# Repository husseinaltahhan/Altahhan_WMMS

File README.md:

# Altahhan_WMMS
WMMS = Welding Machines Monitoring System

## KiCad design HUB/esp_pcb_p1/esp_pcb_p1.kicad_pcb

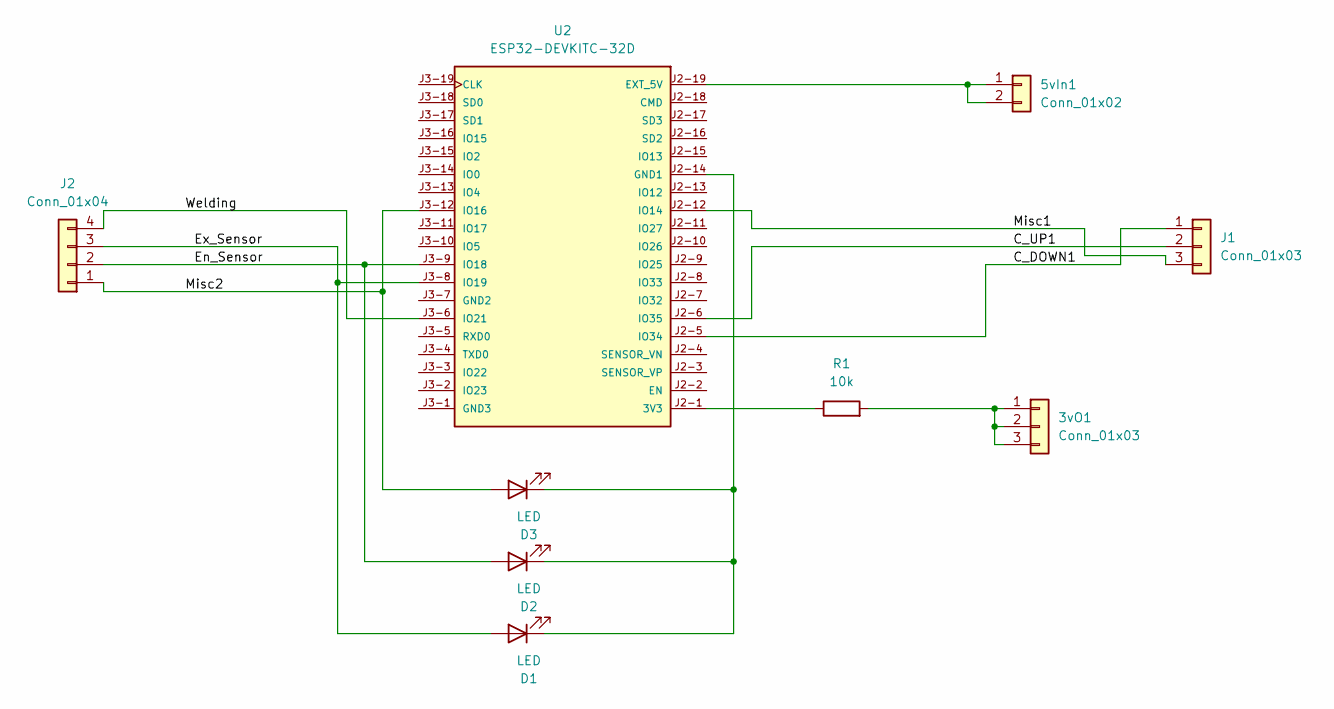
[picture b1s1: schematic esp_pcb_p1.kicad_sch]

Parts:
3vO1: Conn_01x03; TerminalBlock_Phoenix_MKDS-1,5-3-5.08_1x03_P5.08mm_Horizont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
5vIn1: Conn_01x02; TerminalBlock_Phoenix_MKDS-1,5-2-5.08_1x02_P5.08mm_Horizont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
D1, D2, D3: LED; LED_D5.0mm
J1: Conn_01x03; TerminalBlock_Phoenix_MKDS-1,5-3-5.08_1x03_P5.08mm_Horizont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
J2: Conn_01x04; TerminalBlock_Phoenix_MKDS-1,5-4-5.08_1x04_P5.08mm_Horizont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
R1: 10k; R_Axial_DIN0207_L6.3mm_D2.5mm_P7.62mm_Horizontal
U2: ESP32-DEVKITC-32D; MODULE_ESP32-DEVKITC-32D; PARTREV V4

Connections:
/C_DOWN1: J1.1, U2.J2-5 (IO34)
/C_UP1: J1.2, U2.J2-6 (IO35)
/En_Sensor: D2.2 (A), J2.2, U2.J3-9 (IO18)
/Ex_Sensor: D1.2 (A), J2.3, U2.J3-8 (IO19)
/Misc1: J1.3, U2.J2-12 (IO14)
/Misc2: D3.2 (A), J2.1, U2.J3-12 (IO16)
/Welding: J2.4, U2.J3-6 (IO21)
unnamed: 3vO1.1, 3vO1.2, 3vO1.3, R1.2
unnamed: 5vIn1.1, 5vIn1.2, U2.J2-19 (EXT_5V)
unnamed: D1.1 (K), D2.1 (K), D3.1 (K), U2.J2-14 (GND1)
unnamed: R1.1, U2.J2-1 (3V3)

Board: 2 copper layers, 9 parts (0 on the bottom side), 11 nets, no tracks yet.

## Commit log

2025-07-28 testing my git skills
2025-07-28 test 2
2025-07-28 Uploading Project On Github
2025-07-28 Updated main.py & sensor.py with esp code
2025-07-29 Refactor configuration management with environment variables and error handling
2025-07-30 Set up .cursorrules file for future Cursor usage
2025-07-30 Created Two Seperate Files for Welding Detection
    As I'm currently testing two different methodolgies for detection of
    welded cylinders. I seperated both detections into two files and will be
    running tests to finalize my choice soon.
2025-07-30 Changed a bunch of stuff no cap
2025-07-30 Finalized First version of second detection method
2025-08-02 Reworked the second detection system due to bugs
2025-08-02 Fixed a bug in size detection
2025-08-03 Updated communication between ESP, DB, & Central Brain
2025-08-05 Initialized Supabase Client
2025-08-05 Got rid of exposed API key
2025-08-06 Added Reconnection Protocols (Still Incomplete)
2025-08-06 Completed Reconnection Protocol for ESP32 Boards
    If at any point the ESP board Wifi or MQTT broker Client disconnect
    the board will assume a reconnection process in a secondary thread
    until reconnection is successful
2025-08-06 Added Comments and Made Minor Tweaks
2025-08-07 Debugged With Testing
2025-08-10 Converted SQLdb code to supabase code, Added safeties for wifi/mqtt/detection
2025-08-12 debugging IM DEBUGGING
2025-08-12 Fixed bug that never allowed gate detection after welding
2025-08-14 Finalized Raspberry Pi Setup
    Raspberry Pi is now responsible for the MQTT broker and
    running the central_brain.py file to update the supbase
    database. Also made sure to make wifi, mqtt broker, and
    central_brain always run on bootup and reconnect when
    disconnected
2025-08-14 Created foundation for version control on ESP32
2025-08-15 Created First Version of ESP internal Version Ctrl
    Added minimal version control to ESP boards to
    ensure that bad updates that produce errors do not shutdown
    the board.
2025-08-15 Debuged code, Update progress tracking is retained
    Fixed a couple of syntax, logic bugs and added code to make sure
    update progress tracking stays consistent through random reboots.
2025-08-15 Created Cap Welding Detection System
2025-08-16 Hotfixed detection issue
2025-08-16 another attempt at the fix
2025-08-16 another fix
2025-08-16 bro..
2025-08-16 Added an ota setup file
2025-08-17 patched some bugs
